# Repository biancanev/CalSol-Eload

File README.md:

# CalSol-Eload

This project makes use of the template provided in `Excalibur-HW`. Follow the steps listed in the `README` file to make sure all symbols are loaded properly

### Features

#### `power_switch`

The `power_switch` schematic shows the current controller that was simulated in LTSpice. The circuit uses a 

#### Changes to `Root`

A rotary encoder has been added for user input. The plan is to use the switch on the encoder for selection and the 

#### Changes to `Base_Power`

An additional linear regulator has been added to

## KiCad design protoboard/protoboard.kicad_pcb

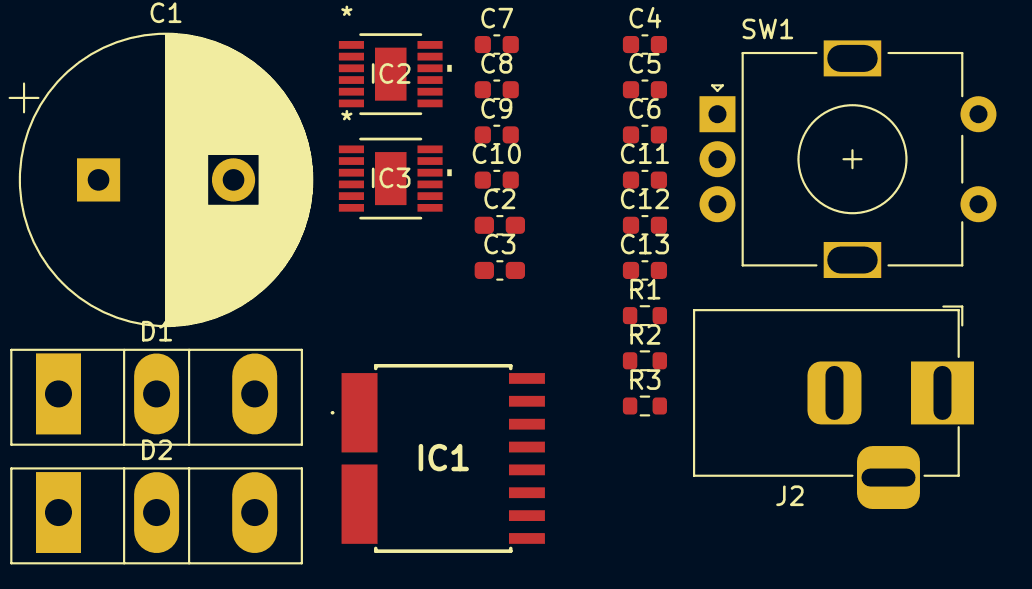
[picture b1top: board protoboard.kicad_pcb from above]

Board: 2 copper layers, 23 parts (0 on the bottom side), 9 nets, no tracks yet.

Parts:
C1: 100u; CP_Radial_D16.0mm_P7.50mm
C2, C3: 1u; C_0603_1608Metric_Pad1.08x0.95mm_HandSolder
C4, C5, C7, C9, C12, C13: 0.1u; C_0603_1608Metric
C6, C8, C10: 10u; C_0603_1608Metric
C11: 10n; C_0603_1608Metric
D1, D2: D; TO-247-3_Vertical
IC1: TMCS1123B1AQDVGR
IC2, IC3: LTC7067RMSE#PBF; 05-08-1666_ADI
J2: Barrel_Jack; BarrelJack_Horizontal
R1, R2, R3: 1k; R_0603_1608Metric
SW1: RotaryEncoder_Switch; RotaryEncoder_Alps_EC11E-Switch_Vertical_H20mm

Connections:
+3V3: C5.1, C6.1
+12V: C2.1, C3.1, C4.1, C7.1, C8.1, C9.1, C10.1, IC2.5 (VCC), IC2.6 (G2VCC), IC2.12 (G1VCC), IC3.5 (VCC), IC3.6 (G2VCC), IC3.12 (G1VCC), J2.1
/A: C13.1, SW1.A
/B: C12.1, SW1.B
/PWM: C11.1, IC2.1 (G1IN), IC3.1 (G1IN)
/power_switch/G1RTN: D2.1 (K), IC2.7 (G2RTN), IC2.10 (G1RTN), IC3.7 (G2RTN), IC3.10 (G1RTN)
/~FLT: IC2.3 (~FLT), IC3.3 (~FLT)
GND: C1.2, C2.2, C3.2, C4.2, C5.2, C6.2, C7.2, C8.2, C9.2, C10.2, C11.2, C12.2, C13.2, D2.2 (A), IC1.2 (IN_-), IC1.3 (GND), IC2.2 (G2IN), IC2.13 (EP), IC3.2 (G2IN), IC3.13 (EP), J2.2, SW1.C, SW1.S2
unnamed: C1.1, D1.2 (A)

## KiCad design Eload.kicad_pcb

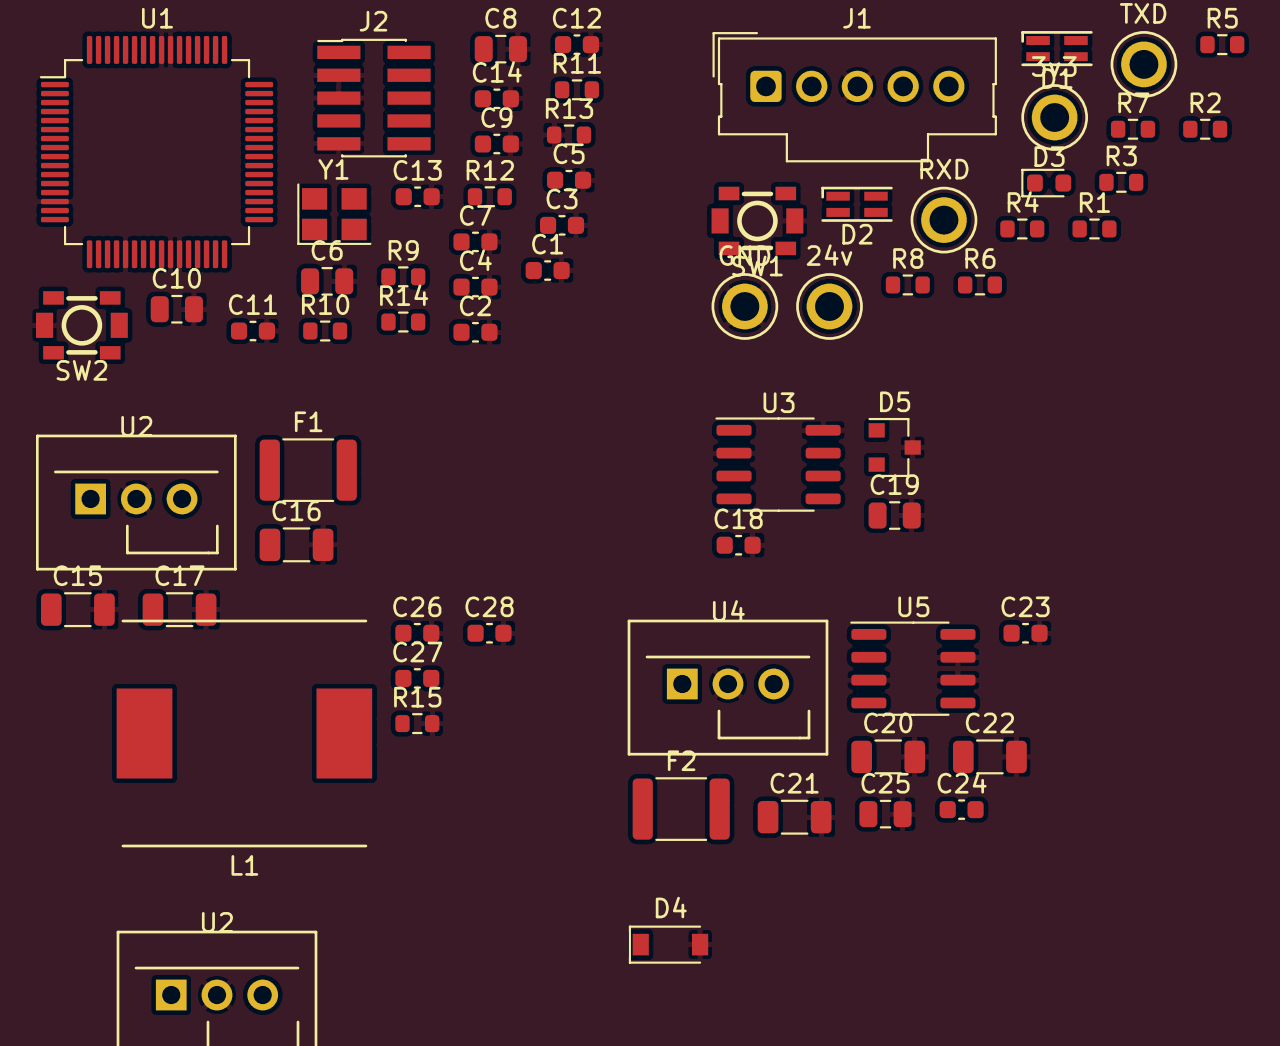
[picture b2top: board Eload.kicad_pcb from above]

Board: 4 copper layers, 67 parts (0 on the bottom side), 33 nets, no tracks yet.

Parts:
C1, C2, C3, C4, C5, C7, C9, C11, C13, C18: 100n; C_0603_1608Metric
C6, C8, C10, C25: 10u; C_0805_2012Metric
C12, C14: 18p; C_0603_1608Metric
C15, C20: 10u; C_1206_3216Metric
C16, C17, C21, C22: 47u; C_1206_3216Metric
C19: DNP; C_0805_2012Metric
C23, C26, C28: 1u; C_0603_1608Metric
C24: 10n; C_0603_1608Metric
C27: 2.2u; C_0603_1608Metric
D1, D2: LED_ABGR; LED_RGB_0606
D3: LED; LED_0603_1608Metric
D4: 3.6V; D_SOD-123
D5: PESD1CAN; SOT-23
F1, F2: 0ZCG0050AF2C; Fuse_1812_4532Metric
J1: CAN; Molex_SL_171971-0005_1x05_P2.54mm_Vertical
J2: SWD; PinHeader_2x05_P1.27mm_Vertical_SMD
L1: 47u; IND13.5mmx12.5mm
R1, R2, R3, R4, R5, R6, R7: 1k; R_0603_1608Metric
R8: 100k; R_0603_1608Metric
R9, R10, R11, R13, R14: 100K; R_0603_1608Metric
R12: 1K; R_0603_1608Metric
R15: 5; R_0603_1608Metric
SW1, SW2: PTS820
TP1: TXD; 1.6MM_TestPoint
TP2: RXD; 1.6MM_TestPoint
TP3: 24v; 1.6MM_TestPoint
TP4: 3v3; 1.6MM_TestPoint
TP5: GND; 1.6MM_TestPoint
U1: LPC1549JDB64; LQFP-64_10x10mm_P0.5mm
U2, U2#2: TPSM84203; TI-SIP_3
U3: SN65HVD230; SOIC-8_3.9x4.9mm_P1.27mm
U4: TPSM84205; TI-SIP_3
U5: LT1763CS8-3.3; SOIC-8_3.9x4.9mm_P1.27mm
Y1: 7V-12.000MAHE-T; Crystal_SMD_TXC_7M-4Pin_3.2x2.5mm

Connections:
+3V3: C1.1, C2.1, C3.1, C4.1, C5.1, C6.1, C7.1, C8.1, C9.1, C10.1, C11.1, C16.1, C17.1, C18.1, C19.1, C24.1, C25.1, D1.1, D2.1, D3.2, D4.1, J2.1, R8.2, R9.2, R10.1, R11.1, R14.1, TP4.1, U1.13, U1.18, U1.20, U1.22, U1.37, U1.41, U1.52, U1.57, U2.3, U2#2.3, U3.3, U5.1, U5.2
+5V: C21.1, C22.1, C23.1, C26.1, L1.1, U4.3, U5.5, U5.8
+5VFiltered: C27.1, C28.1, L1.2
+24V: F1.2, F2.1, J1.2, TP3.1
/CAN/CanH: D5.1, J1.4, U3.7
/CAN/CanL: D5.2, J1.5, U3.6
/CAN_RXD: TP2.1, U1.23, U3.4
/CAN_TXD: TP1.1, U1.3, U3.1
/LED_RGB1_B: R3.2, U1.34
/LED_RGB1_G: R2.2, U1.33
/LED_RGB1_R: R1.2, U1.32
/Micro64/ISP_0: R9.1, U1.54
/Micro64/ISP_1: R10.2, U1.38
/Micro64/SWCLK: J2.4, R13.2, U1.40
/Micro64/SWDIO: J2.2, R14.2, U1.44
/Micro64/SWO: J2.6, U1.59
/Micro64/XTALIN: C14.1, U1.36, Y1.3
/Micro64/XTALOUT: C12.1, U1.35, Y1.1
/Micro64/~RESET~: C13.1, J2.10, R11.2, R12.1, U1.45
/SW1: R8.1, SW1.1
GND: C1.2, C2.2, C3.2, C4.2, C5.2, C6.2, C7.2, C8.2, C9.2, C10.2, C11.2, C12.2, C13.2, C14.2, C15.2, C16.2, C17.2, C18.2, C19.2, C20.2, C21.2, C22.2, C23.2, C25.2, C26.2, C28.2, D4.2, D5.3, J1.3, J2.3, J2.5, J2.9, R13.1, R15.2, SW1.2, SW2.1, TP5.1, U1.14, U1.21, U1.26, U1.27, U1.55, U1.56, U2.2, U2#2.2, U3.2, U3.8, U4.2, U5.3, U5.6, U5.7
unnamed: C15.1, F1.1, U2.1, U2#2.1
unnamed: C20.1, F2.2, U4.1
unnamed: C24.2, U5.4
unnamed: C27.2, R15.1
unnamed: D1.2, R3.1
unnamed: D1.3, R2.1
unnamed: D1.4, R1.1
unnamed: D2.2, R6.1
unnamed: D2.3, R5.1
unnamed: D2.4, R4.1
unnamed: D3.1, R7.1
unnamed: R12.2, SW2.2

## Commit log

2025-01-31 Added kicad
2025-02-10 minor fixes to power delivery
2025-02-17 Added LTSpice sims
2025-02-25 power switch stuff
2025-02-25 finish protoboard v1
2025-02-25 footprint update
2025-03-04 schematic review changes
2025-03-04 forgot to save sch file
